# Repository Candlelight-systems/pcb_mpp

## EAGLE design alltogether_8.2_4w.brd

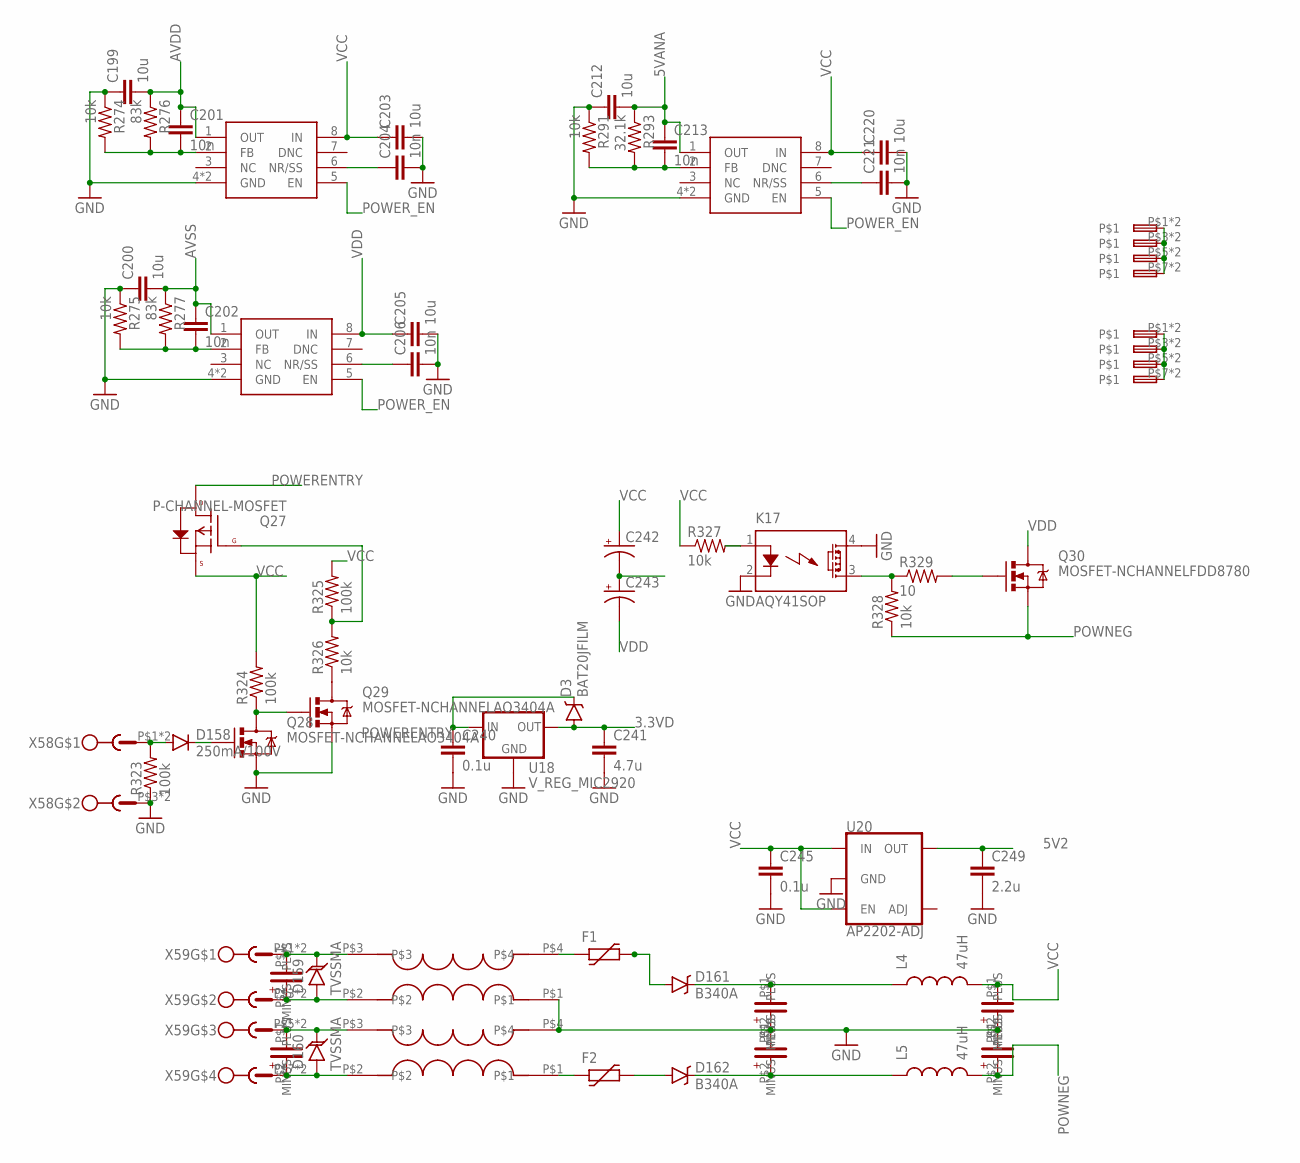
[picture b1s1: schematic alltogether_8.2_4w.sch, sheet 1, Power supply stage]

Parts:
C199, C200, C203, C205, C212, C220: 10u; 0805
C201, C202, C204, C206, C213, C221: 10n; 0402-CAP
C238, C239: CAPACITOR; LLL31
C240, C245: 0.1u; 0402-CAP
C241: 4.7u; 0402-CAP
C242, C243: CAP_POLPTH4; CPOL-RADIAL-1000UF-25V
C246, C247, C250, C251: 1u; LLL31
C249: 2.2u; 0402-CAP
D3: BAT20JFILM; SOD-323
D158: 250mA/100V; SOD-323
D159, D160: TVSSMA; SMA-DIODE
D161, D162: B340A; SMA-DIODE
F1, F2: FUSE_PTC-0805; PTC0805
K17: AQY41SOP; SOP04
L2, L3: COMMONMODEFILTER2014; 2014
L4, L5: 47uH; CR54
Q27: P-CHANNEL-MOSFET; SOT23-3
Q28, Q29: MOSFET-NCHANNELAO3404A; SOT23-3
Q30: MOSFET-NCHANNELFDD8780; DPAK
R274, R275, R291, R326, R327, R328: 10k; 0402-RES
R276, R277: 83k; 0402-RES
R293: 32.1k; 0402-RES
R323, R324, R325: 100k; 0402-RES
R329: 10; 0402-RES
U7, U9: TPS7A49; S-PDSO-G08
U8: TPS7A30; S-PDSO-G08
U18: V_REG_MIC2920; SOT223
U20: AP2202-ADJ; SOT23-5
X1, X2: SPTAF1/4-3.5
X58: SPTA1.5/2
X59: SPTA1.5/4

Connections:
3.3VD: C241.1, D3.A, U18.3 (OUT), X2.P$1, X2.P$2, X2.P$3, X2.P$4, X2.P$5, X2.P$6, X2.P$7, X2.P$8; also elsewhere on the board
5V2: C249.1, U20.5 (OUT); also elsewhere on the board
5VANA: C212.2, C213.1, R293.1, U9.1 (OUT); also elsewhere on the board
AVDD: C199.2, C201.1, R276.1, U7.1 (OUT); also elsewhere on the board
AVSS: C200.2, C202.1, R277.1, U8.1 (OUT); also elsewhere on the board
GND: C199.1, C200.1, C203.2, C204.2, C205.2, C206.2, C212.1, C220.2, C221.2, C240.2, C241.2, C242.-, C243.+, C245.2, C246.P$2 (PLUS), C247.P$1 (MINUS), C249.2, C250.P$2 (PLUS), C251.P$1 (MINUS), K17.2 (K), K17.4 (DS1), L2.P$1, L3.P$4, Q28.2 (S), Q29.2 (S), R274.1, R275.1, R291.1, R323.1, U7.4 (GND), U7.TH (GND), U8.4 (GND), U8.TH (GND), U9.4 (GND), U9.TH (GND), U18.2 (GND), U20.2 (GND), X1.P$1, X1.P$2, X1.P$3, X1.P$4, X1.P$5, X1.P$6, X1.P$7, X1.P$8, X58.P$3, X58.P$4; also elsewhere on the board
unnamed: Q28.3 (D), Q29.1 (G), R324.1
unnamed: Q29.3 (D), R326.1
unnamed: Q27.1 (G), R325.1, R326.2
unnamed: D158.A, R323.2, X58.P$1, X58.P$2
unnamed: K17.3 (DS2), R328.2, R329.1
unnamed: Q30.1 (G), R329.2
unnamed: C239.P$1 (MINUS), D160.C, L3.P$3, X59.P$5, X59.P$6
unnamed: C221.1, U9.6 (NR/SS)
unnamed: C213.2, R291.2, R293.2, U9.2 (FB)
unnamed: K17.1 (A), R327.2
unnamed: C238.P$1 (MINUS), D159.C, L2.P$3, X59.P$1, X59.P$2
unnamed: C246.P$1 (MINUS), D161.C, L4.P$1 (1)
unnamed: C238.P$2 (PLUS), D159.A, L2.P$2, X59.P$3, X59.P$4
unnamed: C239.P$2 (PLUS), D160.A, L3.P$2, X59.P$7, X59.P$8
unnamed: C247.P$2 (PLUS), D162.C, L5.P$1 (1)
unnamed: F1.1, L2.P$4
unnamed: F2.1, L3.P$1
unnamed: C204.1, U7.6 (NR/SS)
unnamed: C201.2, R274.2, R276.2, U7.2 (FB)
unnamed: C206.1, U8.6 (NR/SS)
unnamed: C202.2, R275.2, R277.2, U8.2 (FB)
unnamed: D162.A, F2.2
unnamed: D161.A, F1.2
POWERENTRY: C240.1, D3.C, D158.C, Q27.3 (D), Q28.1 (G), U18.1 (IN)
POWER_EN: U7.5 (EN), U8.5 (EN), U9.5 (EN); also elsewhere on the board
POWNEG: C251.P$2 (PLUS), L5.P$2 (2), Q30.3 (S), R328.1
VCC: C203.1, C220.1, C242.+, C245.1, C250.P$1 (MINUS), L4.P$2 (2), Q27.2 (S), R324.2, R325.2, R327.1, U7.8 (IN), U9.8 (IN), U20.1 (IN), U20.3 (EN); also elsewhere on the board
VDD: C205.1, C243.-, Q30.4 (D), U8.8 (IN); also elsewhere on the board

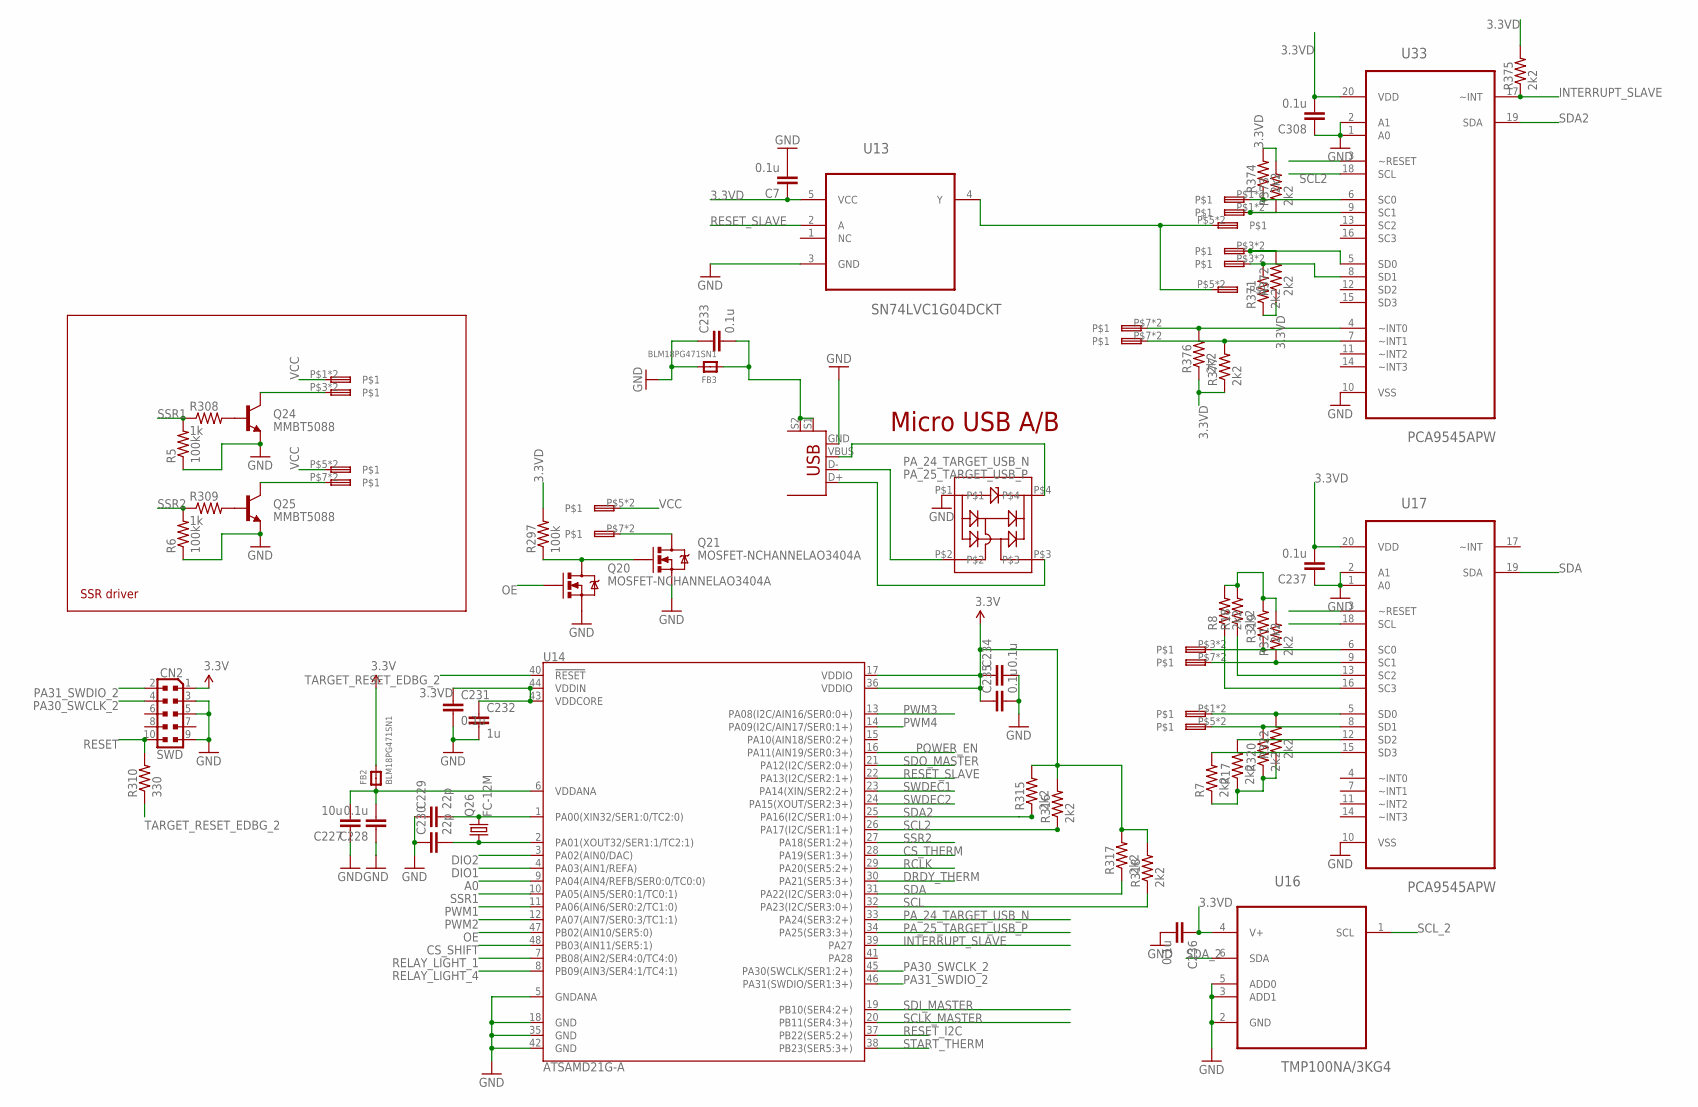
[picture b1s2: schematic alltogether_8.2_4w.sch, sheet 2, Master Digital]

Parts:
C7, C228, C231, C233, C234, C235, C236, C237, C308: 0.1u; 0402-CAP
C227: 10u; 0805
C229, C230: 22p; 0402-CAP
C232: 1u; 0402-CAP
CN2: SWD; CONNETTORI_PINHEAD-2X5-P127
FB2, FB3: BLM18PG471SN1; _0603MP
Q20, Q21: MOSFET-NCHANNELAO3404A; SOT23-3
Q24, Q25: MMBT5088; SOT23-3
Q26: FC-12M
R5, R6, R297: 100k; 0402-RES
R7, R8, R17, R18, R315, R316, R317, R318, R319, R320, R321, R322, R371, R372, R373, R374, R375, R376, R377: 2k2; 0402-RES
R308, R309: 1k; 0402-RES
R310: 330; 0402-RES
U13: SN74LVC1G04DCKT; SOT65P210X110-5N
U14: ATSAMD21G-A; TQFP-48
U16: TMP100NA/3KG4; SOT95P280X145-6N
U17, U33: PCA9545APW; SOP65P640X110-20N
U$15: PRTR5V0U2X
X54, X55, X57, X77, X78: SPTAF1/4-3.5
X56: USB+SHIELD; USB-B-PTH

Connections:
3.3VD: C7.1, C231.1, C232.1, C234.1, C235.1, C236.1, C237.2, C308.2, CN2.1, FB2.2, R7.1, R8.2, R17.1, R18.2, R297.2, R315.2, R316.2, R317.2, R318.2, R319.2, R320.1, R321.2, R322.1, R371.1, R372.1, R373.2, R374.2, R375.2, R376.1, R377.1, U13.5 (VCC), U14.17 (VDDIO), U14.36 (VDDIO), U14.43 (VDDCORE), U14.44 (VDDIN), U16.4 (V+), U17.20 (VDD), U33.20 (VDD); also elsewhere on the board
A0: U14.9 (PA04(AIN4/REFB/SER0:0/TC0:0)); also elsewhere on the board
CS_SHIFT: U14.48 (PB03(AIN11/SER5:1)); also elsewhere on the board
CS_THERM: U14.28 (PA19(SER1:3+)); also elsewhere on the board
DIO1: U14.4 (PA03(AIN1/REFA)); also elsewhere on the board
DIO2: U14.3 (PA02(AIN0/DAC)); also elsewhere on the board
DRDY_THERM: U14.30 (PA21(SER5:3+)); also elsewhere on the board
GND: C7.2, C227.1, C228.1, C229.1, C230.1, C231.2, C232.2, C233.1, C234.2, C235.2, C236.2, C237.1, C308.1, CN2.3, CN2.5, CN2.9, FB3.2, Q20.2 (S), Q21.2 (S), Q24.2 (E), Q25.2 (E), R5.1, R6.1, U13.3 (GND), U14.5 (GNDANA), U14.18 (GND), U14.35 (GND), U14.42 (GND), U16.2 (GND), U16.3 (ADD1), U16.5 (ADD0), U17.1 (A0), U17.2 (A1), U17.10 (VSS), U33.1 (A0), U33.2 (A1), U33.10 (VSS), U$15.P$1, X56.GND; also elsewhere on the board
INTERRUPT_SLAVE: R375.1, U14.39 (PA27), U33.17 (~INT)
unnamed: U13.4 (Y), X77.P$5, X77.P$6, X78.P$5, X78.P$6
unnamed: R374.1, U33.6 (SC0), X77.P$1, X77.P$2
unnamed: R373.1, U33.9 (SC1), X78.P$1, X78.P$2
unnamed: R372.2, U33.5 (SD0), X77.P$3, X77.P$4
unnamed: R371.2, U33.8 (SD1), X78.P$3, X78.P$4
unnamed: R377.2, U33.7 (~INT1), X78.P$7, X78.P$8
unnamed: R376.2, U33.4 (~INT0), X77.P$7, X77.P$8
unnamed: Q24.3 (C), X55.P$3, X55.P$4
unnamed: Q24.1 (B), R308.2
unnamed: Q25.1 (B), R309.2
unnamed: Q25.3 (C), X55.P$7, X55.P$8
unnamed: U$15.P$4, X56.VBUS
unnamed: C229.2, Q26.2, U14.1 (PA00(XIN32/SER1:0/TC2:0))
unnamed: C230.2, Q26.1, U14.2 (PA01(XOUT32/SER1:1/TC2:1))
unnamed: C227.2, C228.2, FB2.1, U14.6 (VDDANA)
unnamed: Q21.3 (D), X54.P$7, X54.P$8
unnamed: Q20.3 (D), Q21.1 (G), R297.1
OE: Q20.1 (G), U14.47 (PB02(AIN10/SER5:0)); also elsewhere on the board
PA30_SWCLK_2: CN2.4, U14.45 (PA30(SWCLK/SER1:2+))
PA31_SWDIO_2: CN2.2, U14.46 (PA31(SWDIO/SER1:3+))
PA_24_TARGET_USB_N: U14.33 (PA24(SER3:2+)), U$15.P$2, X56.D-
PA_25_TARGET_USB_P: U14.34 (PA25(SER3:3+)), U$15.P$3, X56.D+
POWER_EN: U14.16 (PA11(AIN19/SER0:3+)); also elsewhere on the board
PWM1: U14.11 (PA06(AIN6/SER0:2/TC1:0)); also elsewhere on the board
PWM2: U14.12 (PA07(AIN7/SER0:3/TC1:1)); also elsewhere on the board
PWM3: U14.13 (PA08(I2C/AIN16/SER0:0+)); also elsewhere on the board
PWM4: U14.14 (PA09(I2C/AIN17/SER0:1+)); also elsewhere on the board
RCLK: U14.29 (PA20(SER5:2+)); also elsewhere on the board
RELAY_LIGHT_1: U14.7 (PB08(AIN2/SER4:0/TC4:0)); also elsewhere on the board
RELAY_LIGHT_4: U14.8 (PB09(AIN3/SER4:1/TC4:1)); also elsewhere on the board
RESET: CN2.10, R310.2; also elsewhere on the board
RESET_I2C: U14.37 (PB22(SER5:2+)), U17.3 (~RESET)
RESET_SLAVE: U13.2 (A), U14.22 (PA13(I2C/SER2:1+)), U33.3 (~RESET)
SCL: R318.1, U14.32 (PA23(I2C/SER3:0+)), U17.18 (SCL); also elsewhere on the board
SCL2: R316.1, U14.26 (PA17(I2C/SER1:1+)), U33.18 (SCL)
SCLK_MASTER: U14.20 (PB11(SER4:3+)); also elsewhere on the board
SCL_2: R18.1, U16.1 (SCL), U17.13 (SC2)
SCL_3: R8.1, U17.16 (SC3); also elsewhere on the board
SCL_LOCAL_0: R319.1, U17.6 (SC0), X57.P$3, X57.P$4
SCL_LOCAL_1: R321.1, U17.9 (SC1), X57.P$7, X57.P$8
SDA: R317.1, U14.31 (PA22(I2C/SER3:0+)), U17.19 (SDA); also elsewhere on the board
SDA2: R315.1, U14.25 (PA16(I2C/SER1:0+)), U33.19 (SDA)
SDA_2: R17.2, U16.6 (SDA), U17.12 (SD2)
SDA_3: R7.2, U17.15 (SD3); also elsewhere on the board
SDI_MASTER: U14.19 (PB10(SER4:2+)); also elsewhere on the board
SDO_LOCAL_0: R322.2, U17.5 (SD0), X57.P$1, X57.P$2
SDO_LOCAL_1: R320.2, U17.8 (SD1), X57.P$5, X57.P$6
SDO_MASTER: U14.21 (PA12(I2C/SER2:0+)); also elsewhere on the board
SHIELD: C233.2, FB3.1, X56.S1, X56.S2
SSR1: R5.2, R308.1, U14.10 (PA05(AIN5/SER0:1/TC0:1)); also elsewhere on the board
SSR2: R6.2, R309.1, U14.27 (PA18(SER1:2+)); also elsewhere on the board
START_THERM: U14.38 (PB23(SER5:3+)); also elsewhere on the board
SWDEC1: U14.23 (PA14(XIN/SER2:2+)); also elsewhere on the board
SWDEC2: U14.24 (PA15(XOUT/SER2:3+)); also elsewhere on the board
TARGET_RESET_EDBG_2: R310.1, U14.40 (!RESET!)
VCC: X54.P$5, X54.P$6, X55.P$1, X55.P$2, X55.P$5, X55.P$6; also elsewhere on the board

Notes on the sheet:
Micro USB A/B
SSR driver

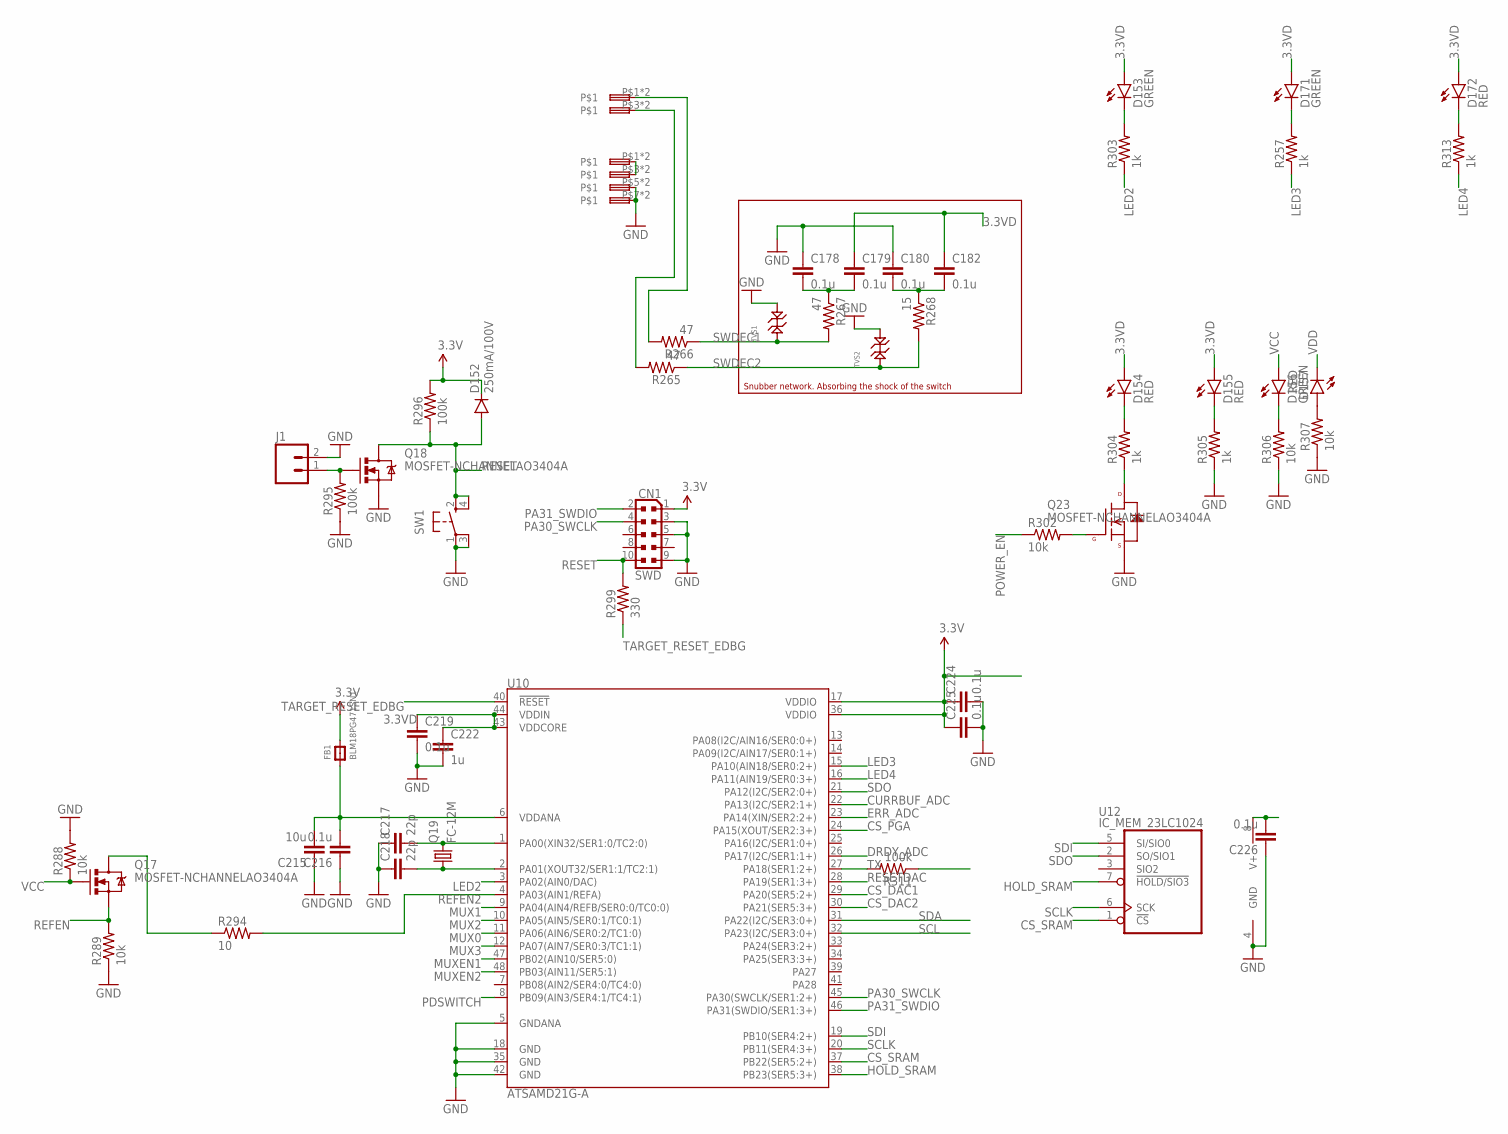
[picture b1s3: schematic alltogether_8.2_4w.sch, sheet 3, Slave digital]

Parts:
C178, C179, C180, C182, C216, C219, C224, C225, C226: 0.1u; 0402-CAP
C215: 10u; 0805
C217, C218: 22p; 0402-CAP
C222: 1u; 0402-CAP
CN1: SWD; CONNETTORI_PINHEAD-2X5-P127
D152: 250mA/100V; SOD-323
D153, D156, D171: GREEN; LED-0603
D154, D155, D157, D172: RED; LED-0603
FB1: BLM18PG471SN1; _0603MP
J1: M02PTH; 1X02
Q17, Q18, Q23: MOSFET-NCHANNELAO3404A; SOT23-3
Q19: FC-12M
R257, R303, R304, R305, R313: 1k; 0402-RES
R265, R266, R267: 47; 0402-RES
R268: 15; 0402-RES
R288, R289, R302, R306, R307: 10k; 0402-RES
R294: 10; 0402-RES
R295, R296, R311: 100k; 0402-RES
R299: 330; 0402-RES
SW1: SPST_TACT-KMR2; KMR2
TVS1, TVS2: TVS_DIODE_SOD-323; SOD-323
U10: ATSAMD21G-A; TQFP-48
U12: IC_MEM_23LC1024; SOIC-8
X52: SPTAF1/2-3.5
X53: SPTAF1/4-3.5

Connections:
3.3VD: C179.1, C182.1, C219.1, C222.1, C224.1, C225.1, C226.2, CN1.1, D152.C, D153.A, D154.A, D155.A, D171.A, D172.A, FB1.2, R296.2, U10.17 (VDDIO), U10.36 (VDDIO), U10.43 (VDDCORE), U10.44 (VDDIN), U12.8 (V+), X53.P$1, X53.P$2, X53.P$3, X53.P$4; also elsewhere on the board
CS_DAC1: U10.29 (PA20(SER5:2+)); also elsewhere on the board
CS_DAC2: U10.30 (PA21(SER5:3+)); also elsewhere on the board
CS_PGA: U10.24 (PA15(XOUT/SER2:3+)); also elsewhere on the board
CS_SRAM: U10.37 (PB22(SER5:2+)), U12.1 (!CS)
CURRBUF_ADC: U10.22 (PA13(I2C/SER2:1+)); also elsewhere on the board
DRDY_ADC: U10.26 (PA17(I2C/SER1:1+)); also elsewhere on the board
ERR_ADC: U10.23 (PA14(XIN/SER2:2+)); also elsewhere on the board
GND: C178.1, C180.1, C215.1, C216.1, C217.1, C218.1, C219.2, C222.2, C224.2, C225.2, C226.1, CN1.3, CN1.5, CN1.9, J1.2, Q18.2 (S), Q23.2 (S), R288.2, R289.1, R295.1, R305.1, R306.1, R307.1, SW1.1, SW1.3 (P1), TVS1.CATH, TVS2.CATH, U10.5 (GNDANA), U10.18 (GND), U10.35 (GND), U10.42 (GND), U12.4 (GND), X53.P$5, X53.P$6, X53.P$7, X53.P$8; also elsewhere on the board
HOLD_SRAM: U10.38 (PB23(SER5:3+)), U12.7 (!HOLD/SIO3)
LED2: R303.1, U10.3 (PA02(AIN0/DAC))
LED3: R257.1, U10.15 (PA10(AIN18/SER0:2+))
LED4: R313.1, U10.16 (PA11(AIN19/SER0:3+))
MOSFETDRIVE2: Q23.1 (G), R302.2
MUX0: U10.11 (PA06(AIN6/SER0:2/TC1:0)); also elsewhere on the board
MUX1: U10.9 (PA04(AIN4/REFB/SER0:0/TC0:0)); also elsewhere on the board
MUX2: U10.10 (PA05(AIN5/SER0:1/TC0:1)); also elsewhere on the board
MUX3: U10.12 (PA07(AIN7/SER0:3/TC1:1)); also elsewhere on the board
MUXEN1: U10.47 (PB02(AIN10/SER5:0)); also elsewhere on the board
MUXEN2: U10.48 (PB03(AIN11/SER5:1)); also elsewhere on the board
unnamed: D171.C, R257.2
unnamed: D172.C, R313.2
unnamed: C217.2, Q19.2, U10.1 (PA00(XIN32/SER1:0/TC2:0))
unnamed: C218.2, Q19.1, U10.2 (PA01(XOUT32/SER1:1/TC2:1))
unnamed: C215.2, C216.2, FB1.1, U10.6 (VDDANA)
unnamed: D155.C, R305.2
unnamed: D156.C, R306.2
unnamed: D154.C, R304.2
unnamed: Q23.3 (D), R304.1
unnamed: D157.A, R307.2
unnamed: J1.1, Q18.1 (G), R295.2
unnamed: D153.C, R303.2
unnamed: Q17.3 (D), R294.1
unnamed: C178.2, C179.2, R267.1
unnamed: C180.2, C182.2, R268.1
PA30_SWCLK: CN1.4, U10.45 (PA30(SWCLK/SER1:2+))
PA31_SWDIO: CN1.2, U10.46 (PA31(SWDIO/SER1:3+))
PDSWITCH: U10.8 (PB09(AIN3/SER4:1/TC4:1)); also elsewhere on the board
POWER_EN: R302.1; also elsewhere on the board
REFEN: Q17.2 (S), R289.2; also elsewhere on the board
REFEN2: R294.2, U10.4 (PA03(AIN1/REFA))
RESET: CN1.10, D152.A, Q18.3 (D), R296.1, R299.2, SW1.2 (S), SW1.4 (S1); also elsewhere on the board
RESETDAC: U10.28 (PA19(SER1:3+)); also elsewhere on the board
SCL: R311.1, U10.32 (PA23(I2C/SER3:0+)); also elsewhere on the board
SCLK: U10.20 (PB11(SER4:3+)), U12.6 (SCK); also elsewhere on the board
SDA: U10.31 (PA22(I2C/SER3:0+)); also elsewhere on the board
SDI: U10.19 (PB10(SER4:2+)), U12.5 (SI/SIO0); also elsewhere on the board
SDO: U10.21 (PA12(I2C/SER2:0+)), U12.2 (SO/SIO1); also elsewhere on the board
SWDEC1: R266.1, R267.2, TVS1.ANODE; also elsewhere on the board
SWDEC1IN: R266.2, X52.P$1, X52.P$2
SWDEC2: R265.1, R268.2, TVS2.ANODE; also elsewhere on the board
SWDEC2IN: R265.2, X52.P$3, X52.P$4
TARGET_RESET_EDBG: R299.1, U10.40 (!RESET!)
TX: R311.2, U10.27 (PA18(SER1:2+))
VCC: D156.A, Q17.1 (G), R288.1; also elsewhere on the board
VDD: D157.C; also elsewhere on the board

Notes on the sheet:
Snubber network. Absorbing the shock of the switch

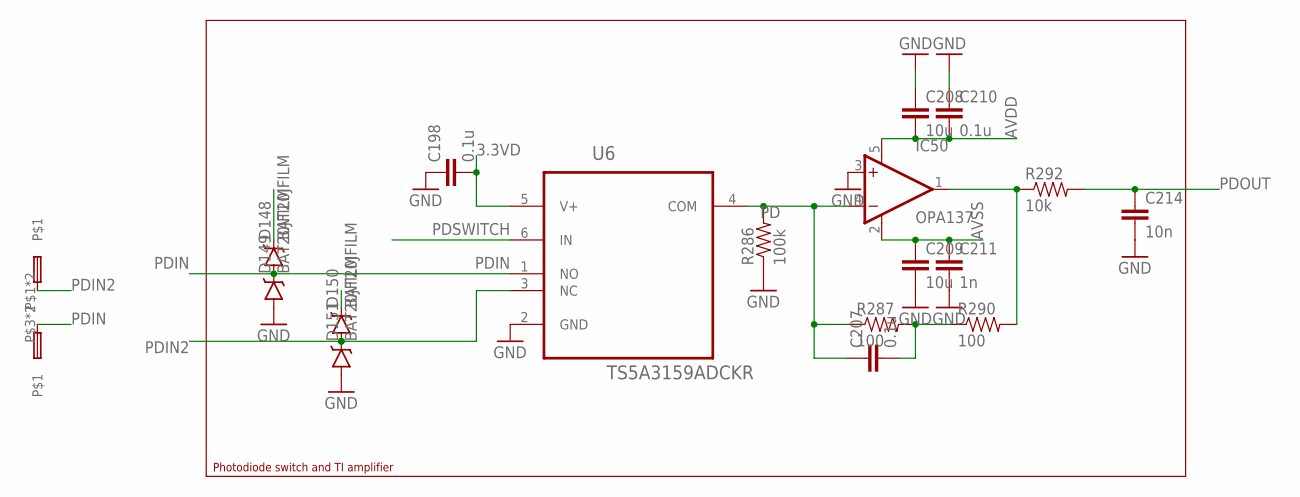
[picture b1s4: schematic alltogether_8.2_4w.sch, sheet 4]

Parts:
C198, C207, C210: 0.1u; 0402-CAP
C208, C209: 10u; 0805
C211: 1n; 0402-CAP
C214: 10n; 0402-CAP
D148, D149, D150, D151: BAT20JFILM; SOD-323
IC50: OPA137; SOT23-5
R286: 100k; 0402-RES
R287, R290: 100; 0805
R292: 10k; 0402-RES
U6: TS5A3159ADCKR; SOT65P210X110-6N
X4: SPTAF1/2-3.5

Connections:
3.3VD: C198.2, D148.C, D150.C, U6.5 (V+); also elsewhere on the board
AVDD: C208.2, C210.2, IC50.5 (V+); also elsewhere on the board
AVSS: C209.1, C211.1, IC50.2 (V-); also elsewhere on the board
GND: C198.1, C208.1, C209.2, C210.1, C211.2, C214.2, D149.A, D151.A, IC50.3 (+IN), R286.1, U6.2 (GND); also elsewhere on the board
unnamed: IC50.1 (OUT), R290.2, R292.1
unnamed: C207.2, R287.2, R290.1
PD: C207.1, IC50.4 (-IN), R286.2, R287.1, U6.4 (COM)
PDIN: D148.A, D149.C, U6.1 (NO), X4.P$3, X4.P$4
PDIN2: D150.A, D151.C, U6.3 (NC), X4.P$1, X4.P$2
PDOUT: C214.1, R292.2; also elsewhere on the board
PDSWITCH: U6.6 (IN); also elsewhere on the board

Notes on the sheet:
Photodiode switch and TI amplifier

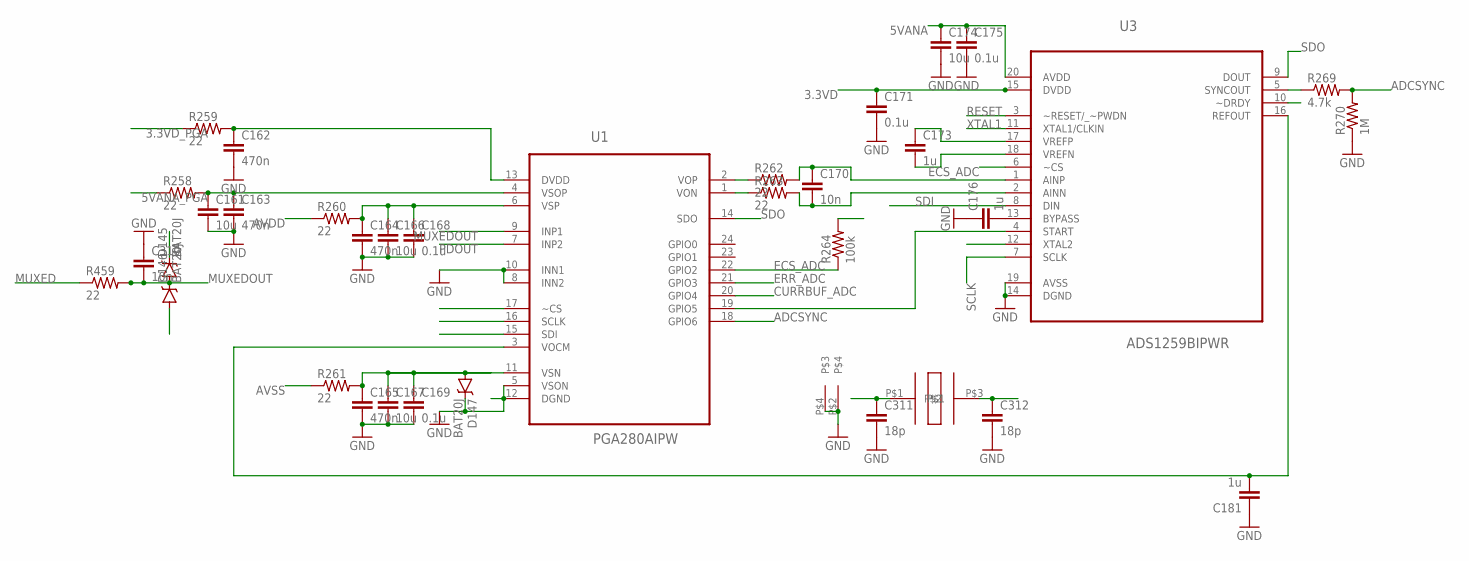
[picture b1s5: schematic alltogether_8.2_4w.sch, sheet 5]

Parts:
C161, C166, C167, C174: 10u; 0805
C162, C163, C164, C165: 470n; 0402-CAP
C168, C169, C171, C175: 0.1u; 0402-CAP
C170, C310: 10n; 0402-CAP
C173, C176, C181: 1u; 0402-CAP
C311, C312: 18p; 0402-CAP
D145, D146, D147: BAT20J; SOD-323
R258, R259, R260, R261, R262, R263, R459: 22; 0402-RES
R264: 100k; 0402-RES
R269: 4.7k; 0402-RES
R270: 1M; 0402-RES
U1: PGA280AIPW; SOP65P640X120-24N
U3: ADS1259BIPWR; SOP65P640X120-20N
U$1: ABMM2

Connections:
3.3VD: C171.1, R259.1, R264.2, U3.15 (DVDD); also elsewhere on the board
3.3VD_PGA: C162.1, R259.2, U1.13 (DVDD)
5VANA: C174.1, C175.1, R258.1, U3.20 (AVDD); also elsewhere on the board
5VANA_PGA: C161.1, C163.1, R258.2, U1.4 (VSOP)
ADCSYNC: R269.2, R270.2, U1.18 (GPIO6)
AVDD: D145.C, R260.1; also elsewhere on the board
AVSS: D146.A, R261.1; also elsewhere on the board
CS_PGA: U1.17 (~CS); also elsewhere on the board
CURRBUF_ADC: U1.20 (GPIO4); also elsewhere on the board
DRDY_ADC: U3.10 (~DRDY); also elsewhere on the board
ECS_ADC: R264.1, U1.22 (GPIO2), U3.6 (~CS)
ERR_ADC: U1.21 (GPIO3); also elsewhere on the board
GND: C161.2, C162.2, C163.2, C164.2, C165.2, C166.2, C167.2, C168.2, C169.2, C171.2, C174.2, C175.2, C176.1, C181.1, C310.1, C311.2, C312.2, D147.C, R270.1, U1.5 (VSON), U1.8 (INN2), U1.10 (INN1), U1.12 (DGND), U3.14 (DGND), U3.19 (AVSS), U$1.P$2, U$1.P$4; also elsewhere on the board
MUXED: R459.1; also elsewhere on the board
MUXEDOUT: C310.2, D145.A, D146.C, R459.2, U1.9 (INP1)
unnamed: R262.1, U1.2 (VOP)
unnamed: R263.1, U1.1 (VON)
unnamed: C170.1, R262.2, U3.1 (AINP)
unnamed: C170.2, R263.2, U3.2 (AINN)
unnamed: C181.2, U1.3 (VOCM), U3.16 (REFOUT)
unnamed: R269.1, U3.5 (SYNCOUT)
unnamed: U1.19 (GPIO5), U3.4 (START)
unnamed: C164.1, C166.1, C168.1, R260.2, U1.6 (VSP)
unnamed: C176.2, U3.13 (BYPASS)
unnamed: C165.1, C167.1, C169.1, D147.A, R261.2, U1.11 (VSN)
unnamed: C173.1, U3.17 (VREFP)
unnamed: C173.2, U3.18 (VREFN)
PDOUT: U1.7 (INP2); also elsewhere on the board
RESET: U3.3 (~RESET/_~PWDN); also elsewhere on the board
SCLK: U1.16 (SCLK), U3.7 (SCLK); also elsewhere on the board
SDI: U1.15 (SDI), U3.8 (DIN); also elsewhere on the board
SDO: U1.14 (SDO), U3.9 (DOUT); also elsewhere on the board
XTAL1: C311.1, U3.11 (XTAL1/CLKIN), U$1.P$1
XTAL2: C312.1, U3.12 (XTAL2), U$1.P$3

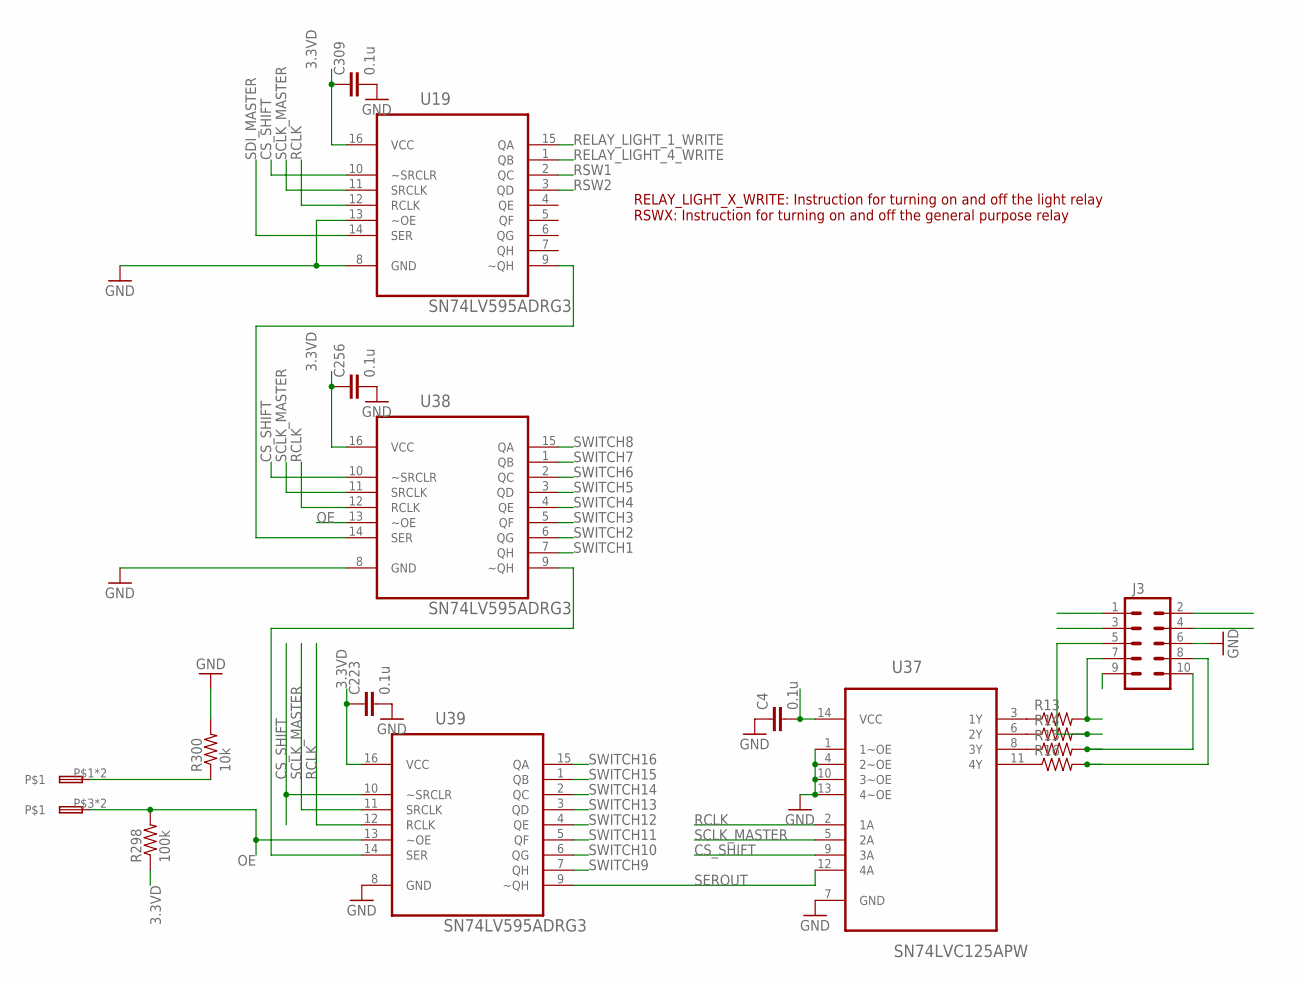
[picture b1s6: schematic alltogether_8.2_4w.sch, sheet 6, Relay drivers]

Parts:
C4, C223, C256, C309: 0.1u; 0402-CAP
J3: M05X2SHD; 2X5-SHROUDED
R13, R14, R15, R16: RESISTOR0402; 0402-RES
R298: 100k; 0402-RES
R300: 10k; 0402-RES
U19, U38, U39: SN74LV595ADRG3; SOIC127P600X175-16N
U37: SN74LVC125APW; SOP65P640X120-14N
X54: SPTAF1/4-3.5

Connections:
3.3VD: C4.2, C223.1, C256.1, C309.1, J3.9, R298.1, U19.16 (VCC), U37.14 (VCC), U38.16 (VCC), U39.16 (VCC); also elsewhere on the board
CS_SHIFT: U19.10 (~SRCLR), U37.9 (3A), U38.10 (~SRCLR), U39.10 (~SRCLR); also elsewhere on the board
CS_SHIFT_BUFFERED: J3.10, R15.2
DIO1: J3.1; also elsewhere on the board
DIO2: J3.2; also elsewhere on the board
GND: C4.1, C223.2, C256.2, C309.2, J3.6, R300.2, U19.8 (GND), U19.13 (~OE), U37.1 (1~OE), U37.4 (2~OE), U37.7 (GND), U37.10 (3~OE), U37.13 (4~OE), U38.8 (GND), U39.8 (GND); also elsewhere on the board
unnamed: R16.1, U37.11 (4Y)
unnamed: R15.1, U37.8 (3Y)
unnamed: R14.1, U37.6 (2Y)
unnamed: R13.1, U37.3 (1Y)
unnamed: R300.1, X54.P$1, X54.P$2
OE: R298.2, U38.13 (~OE), U39.13 (~OE), X54.P$3, X54.P$4; also elsewhere on the board
RCLK: U19.12 (RCLK), U37.2 (1A), U38.12 (RCLK), U39.12 (RCLK); also elsewhere on the board
RCLK_BUFFERED: J3.7, R13.2
RELAY_LIGHT_1_WRITE: U19.15 (QA); also elsewhere on the board
RELAY_LIGHT_4_WRITE: U19.1 (QB); also elsewhere on the board
RSW1: U19.2 (QC); also elsewhere on the board
RSW2: U19.3 (QD); also elsewhere on the board
SCLK_MASTER: U19.11 (SRCLK), U37.5 (2A), U38.11 (SRCLK), U39.11 (SRCLK); also elsewhere on the board
SCLK_MASTER_BUFFERED: J3.5, R14.2
SCL_3: J3.4; also elsewhere on the board
SDA_3: J3.3; also elsewhere on the board
SDI_MASTER: U19.14 (SER); also elsewhere on the board
SEROUT: U37.12 (4A), U39.9 (~QH)
SEROUT_BUFFERED: J3.8, R16.2
SHIFT_SERIN: U38.9 (~QH), U39.14 (SER)
SHIFT_SERIN1: U19.9 (~QH), U38.14 (SER)
SWITCH1: U38.7 (QH); also elsewhere on the board
SWITCH2: U38.6 (QG); also elsewhere on the board
SWITCH3: U38.5 (QF); also elsewhere on the board
SWITCH4: U38.4 (QE); also elsewhere on the board
SWITCH5: U38.3 (QD); also elsewhere on the board
SWITCH6: U38.2 (QC); also elsewhere on the board
SWITCH7: U38.1 (QB); also elsewhere on the board
SWITCH8: U38.15 (QA); also elsewhere on the board
SWITCH9: U39.7 (QH); also elsewhere on the board
SWITCH10: U39.6 (QG); also elsewhere on the board
SWITCH11: U39.5 (QF); also elsewhere on the board
SWITCH12: U39.4 (QE); also elsewhere on the board
SWITCH13: U39.3 (QD); also elsewhere on the board
SWITCH14: U39.2 (QC); also elsewhere on the board
SWITCH15: U39.1 (QB); also elsewhere on the board
SWITCH16: U39.15 (QA); also elsewhere on the board

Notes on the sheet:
RELAY_LIGHT_X_WRITE: Instruction for turning on and off the light relay RSWX: Instruction for turning on and off the general purpose relay

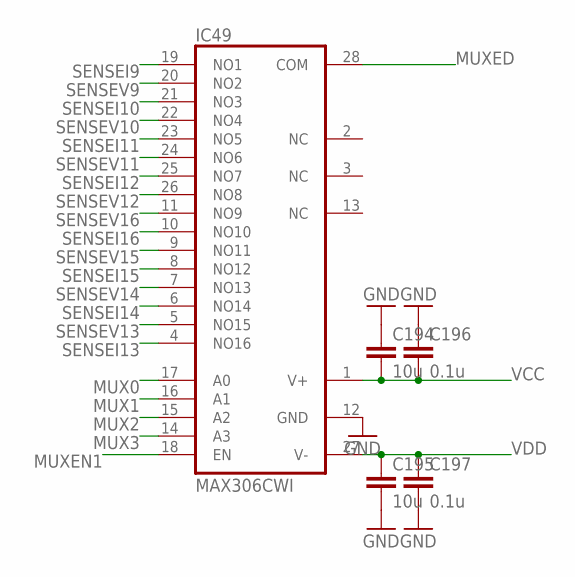
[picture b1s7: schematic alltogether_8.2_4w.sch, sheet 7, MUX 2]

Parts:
C194, C195: 10u; 0805
C196, C197: 0.1u; 0402-CAP
IC49: MAX306CWI; SO28L

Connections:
GND: C194.1, C195.2, C196.1, C197.2, IC49.12 (GND); also elsewhere on the board
MUX0: IC49.17 (A0); also elsewhere on the board
MUX1: IC49.16 (A1); also elsewhere on the board
MUX2: IC49.15 (A2); also elsewhere on the board
MUX3: IC49.14 (A3); also elsewhere on the board
MUXED: IC49.28 (COM); also elsewhere on the board
MUXEN1: IC49.18 (EN); also elsewhere on the board
SENSEI9: IC49.19 (NO1); also elsewhere on the board
SENSEI10: IC49.21 (NO3); also elsewhere on the board
SENSEI11: IC49.23 (NO5); also elsewhere on the board
SENSEI12: IC49.25 (NO7); also elsewhere on the board
SENSEI13: IC49.4 (NO16); also elsewhere on the board
SENSEI14: IC49.6 (NO14); also elsewhere on the board
SENSEI15: IC49.8 (NO12); also elsewhere on the board
SENSEI16: IC49.10 (NO10); also elsewhere on the board
SENSEV9: IC49.20 (NO2); also elsewhere on the board
SENSEV10: IC49.22 (NO4); also elsewhere on the board
SENSEV11: IC49.24 (NO6); also elsewhere on the board
SENSEV12: IC49.26 (NO8); also elsewhere on the board
SENSEV13: IC49.5 (NO15); also elsewhere on the board
SENSEV14: IC49.7 (NO13); also elsewhere on the board
SENSEV15: IC49.9 (NO11); also elsewhere on the board
SENSEV16: IC49.11 (NO9); also elsewhere on the board
VCC: C194.2, C196.2, IC49.1 (V+); also elsewhere on the board
VDD: C195.1, C197.1, IC49.27 (V-); also elsewhere on the board

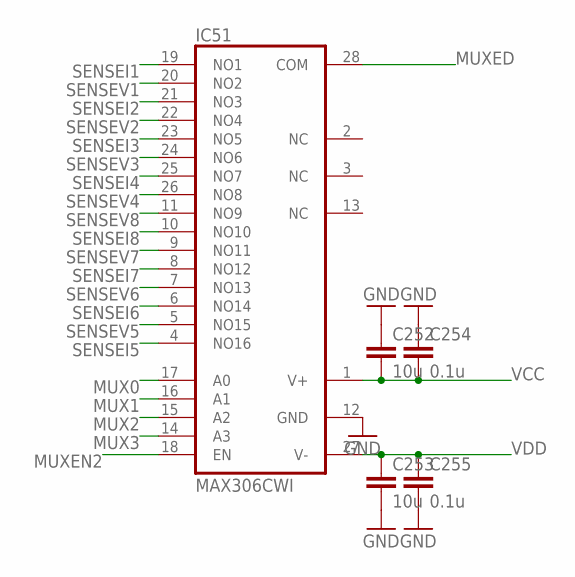
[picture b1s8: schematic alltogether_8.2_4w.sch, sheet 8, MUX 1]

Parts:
C252, C253: 10u; 0805
C254, C255: 0.1u; 0402-CAP
IC51: MAX306CWI; SO28L

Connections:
GND: C252.1, C253.2, C254.1, C255.2, IC51.12 (GND); also elsewhere on the board
MUX0: IC51.17 (A0); also elsewhere on the board
MUX1: IC51.16 (A1); also elsewhere on the board
MUX2: IC51.15 (A2); also elsewhere on the board
MUX3: IC51.14 (A3); also elsewhere on the board
MUXED: IC51.28 (COM); also elsewhere on the board
MUXEN2: IC51.18 (EN); also elsewhere on the board
SENSEI1: IC51.19 (NO1); also elsewhere on the board
SENSEI2: IC51.21 (NO3); also elsewhere on the board
SENSEI3: IC51.23 (NO5); also elsewhere on the board
SENSEI4: IC51.25 (NO7); also elsewhere on the board
SENSEI5: IC51.4 (NO16); also elsewhere on the board
SENSEI6: IC51.6 (NO14); also elsewhere on the board
SENSEI7: IC51.8 (NO12); also elsewhere on the board
SENSEI8: IC51.10 (NO10); also elsewhere on the board
SENSEV1: IC51.20 (NO2); also elsewhere on the board
SENSEV2: IC51.22 (NO4); also elsewhere on the board
SENSEV3: IC51.24 (NO6); also elsewhere on the board
SENSEV4: IC51.26 (NO8); also elsewhere on the board
SENSEV5: IC51.5 (NO15); also elsewhere on the board
SENSEV6: IC51.7 (NO13); also elsewhere on the board
SENSEV7: IC51.9 (NO11); also elsewhere on the board
SENSEV8: IC51.11 (NO9); also elsewhere on the board
VCC: C252.2, C254.2, IC51.1 (V+); also elsewhere on the board
VDD: C253.1, C255.1, IC51.27 (V-); also elsewhere on the board

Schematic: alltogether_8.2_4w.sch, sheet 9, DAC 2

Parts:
C172, C187, C188, C189, C191, C192, C193: 0.1u; 0402-CAP
C177: 2.2u; 0402-CAP
C183, C184, C185, C186: 10u; 0805
C190: 1u; 0402-CAP
R271, R272, R273: 10k; 0402-RES
TP1, TP2, TP3: TEST-POINT3; PAD.03X.03
U2: AP2202-ADJ; SOT23-5
U4: REF3225AMDBVREPG4; SOT95P280X145-6N
U5: DAC7718SRGZRQFP; QFP50P1200X1200X160-64N

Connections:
3.3V: C177.1, C190.2, C191.1, C193.2, R271.1, R272.1, R273.2, U2.5 (OUT), U4.4 (IN), U5.24 (DVDD), U5.55 (IOVDD), U5.56 (DVDD_2)
AVDD: C172.1, C183.1, C185.1, C187.1, C188.1, U2.1 (IN), U2.3 (EN), U5.1 (AVDD), U5.48 (AVDD_2); also elsewhere on the board
AVSS: C184.2, C186.2, C189.2, C192.2, U5.12 (AVSS), U5.37 (AVSS_2); also elsewhere on the board
CS_DAC1: R272.2, U5.58 (~CS); also elsewhere on the board
DAC9: U5.11 (VOUT-0); also elsewhere on the board
DAC10: U5.7 (VOUT-1); also elsewhere on the board
DAC11: U5.6 (VOUT-2); also elsewhere on the board
DAC12: U5.4 (VOUT-3); also elsewhere on the board
DAC13: U5.45 (VOUT-4); also elsewhere on the board
DAC14: U5.43 (VOUT-5); also elsewhere on the board
DAC15: U5.42 (VOUT-6); also elsewhere on the board
DAC16: U5.38 (VOUT-7); also elsewhere on the board
GND: C172.2, C177.2, C183.2, C184.1, C185.2, C186.1, C187.2, C188.2, C189.1, C190.1, C191.2, C192.1, C193.1, U2.2 (GND), U4.1 (GND_F), U4.2 (GND_S), U5.8 (AGND-A), U5.9 (AGND-A_2), U5.25 (DGND), U5.28 (DGND_2), U5.40 (AGND-B), U5.41 (AGND-B_2), U5.50 (~USB/BTC), U5.54 (DGND_3), U5.62 (~LDAC), U5.63 (~WAKEUP); also elsewhere on the board
unnamed: TP1.P$1, U5.10 (OFFSET-A)
unnamed: R271.2, U5.51 (RSTSEL)
unnamed: R273.1, U5.20 (~CLR)
unnamed: TP2.P$1, U5.39 (OFFSET-B)
unnamed: TP3.P$1, U5.14 (VMON)
unnamed: U4.5 (OUT_S), U4.6 (OUT_F), U5.5 (REF-A), U5.44 (REF-B)
REFEN: U4.3 (ENABLE); also elsewhere on the board
RESETDAC: U5.21 (~RST); also elsewhere on the board
SCLK: U5.57 (SCLK); also elsewhere on the board
SDI: U5.59 (SDI); also elsewhere on the board
SDO: U5.61 (SDO); also elsewhere on the board

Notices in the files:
parts and their libraries:
microbuilder: This work is placed in the public domain, and may be freely used for commercial and non-commercial work with the following conditions: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
SparkFun-DiscreteSemi: Licensing: Creative Commons ShareAlike 4.0 International - https://creativecommons.org/licenses/by-sa/4.0
